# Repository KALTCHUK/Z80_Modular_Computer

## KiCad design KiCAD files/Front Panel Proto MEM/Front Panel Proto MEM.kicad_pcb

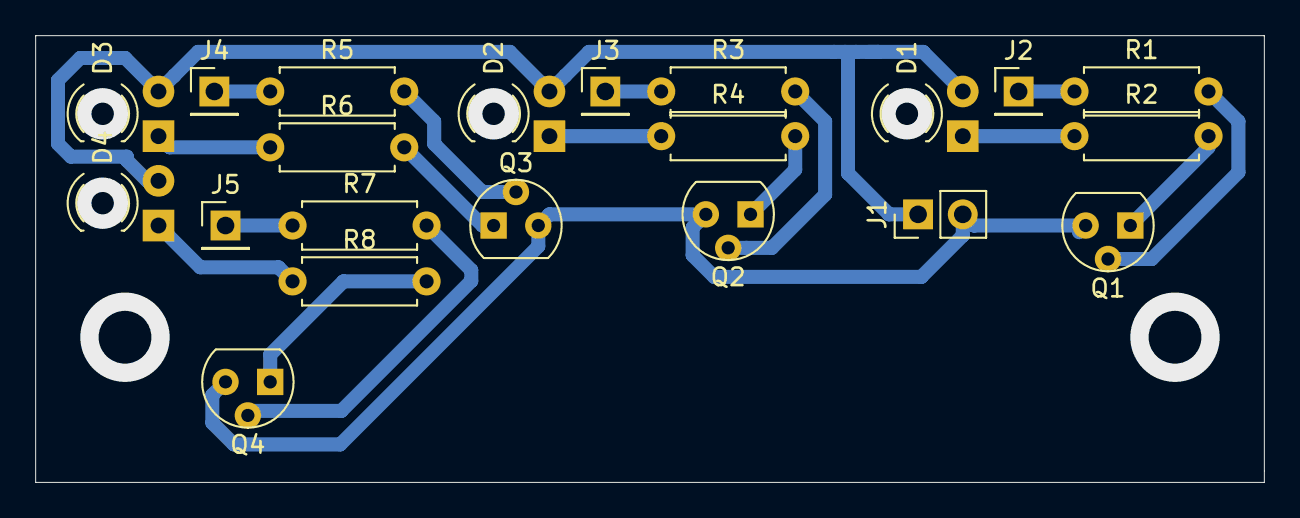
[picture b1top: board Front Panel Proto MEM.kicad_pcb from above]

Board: 2 copper layers, 69.9 x 25.4 mm, 21 parts (0 on the bottom side), 18 nets.

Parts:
D1, D2, D3, D4: LED; LED_D3.0mm
J1: Conn; PinHeader_1x02_P2.54mm_Vertical
J2, J3, J4, J5: Conn; PinHeader_1x01_P2.54mm_Vertical
Q1, Q2, Q3, Q4: BC547; TO-92_Inline
R1, R3, R5, R7: 10k; R_Axial_DIN0207_L6.3mm_D2.5mm_P7.62mm_Horizontal
R2, R4, R6, R8: 470; R_Axial_DIN0207_L6.3mm_D2.5mm_P7.62mm_Horizontal

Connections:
+5V: D1.2, D2.2, D3.2, D4.2, J1.1
GND: J1.2, Q1.3, Q2.3, Q3.3, Q4.3
unnamed: D1.1, R2.1
unnamed: D2.1, R4.1
unnamed: D3.1, R6.1
unnamed: D4.1, R8.1
unnamed: J2.1, R1.1
unnamed: J3.1, R3.1
unnamed: J4.1, R5.1
unnamed: J5.1, R7.1
unnamed: Q1.1, R2.2
unnamed: Q1.2, R1.2
unnamed: Q2.1, R4.2
unnamed: Q2.2, R3.2
unnamed: Q3.1, R6.2
unnamed: Q3.2, R5.2
unnamed: Q4.1, R8.2
unnamed: Q4.2, R7.2

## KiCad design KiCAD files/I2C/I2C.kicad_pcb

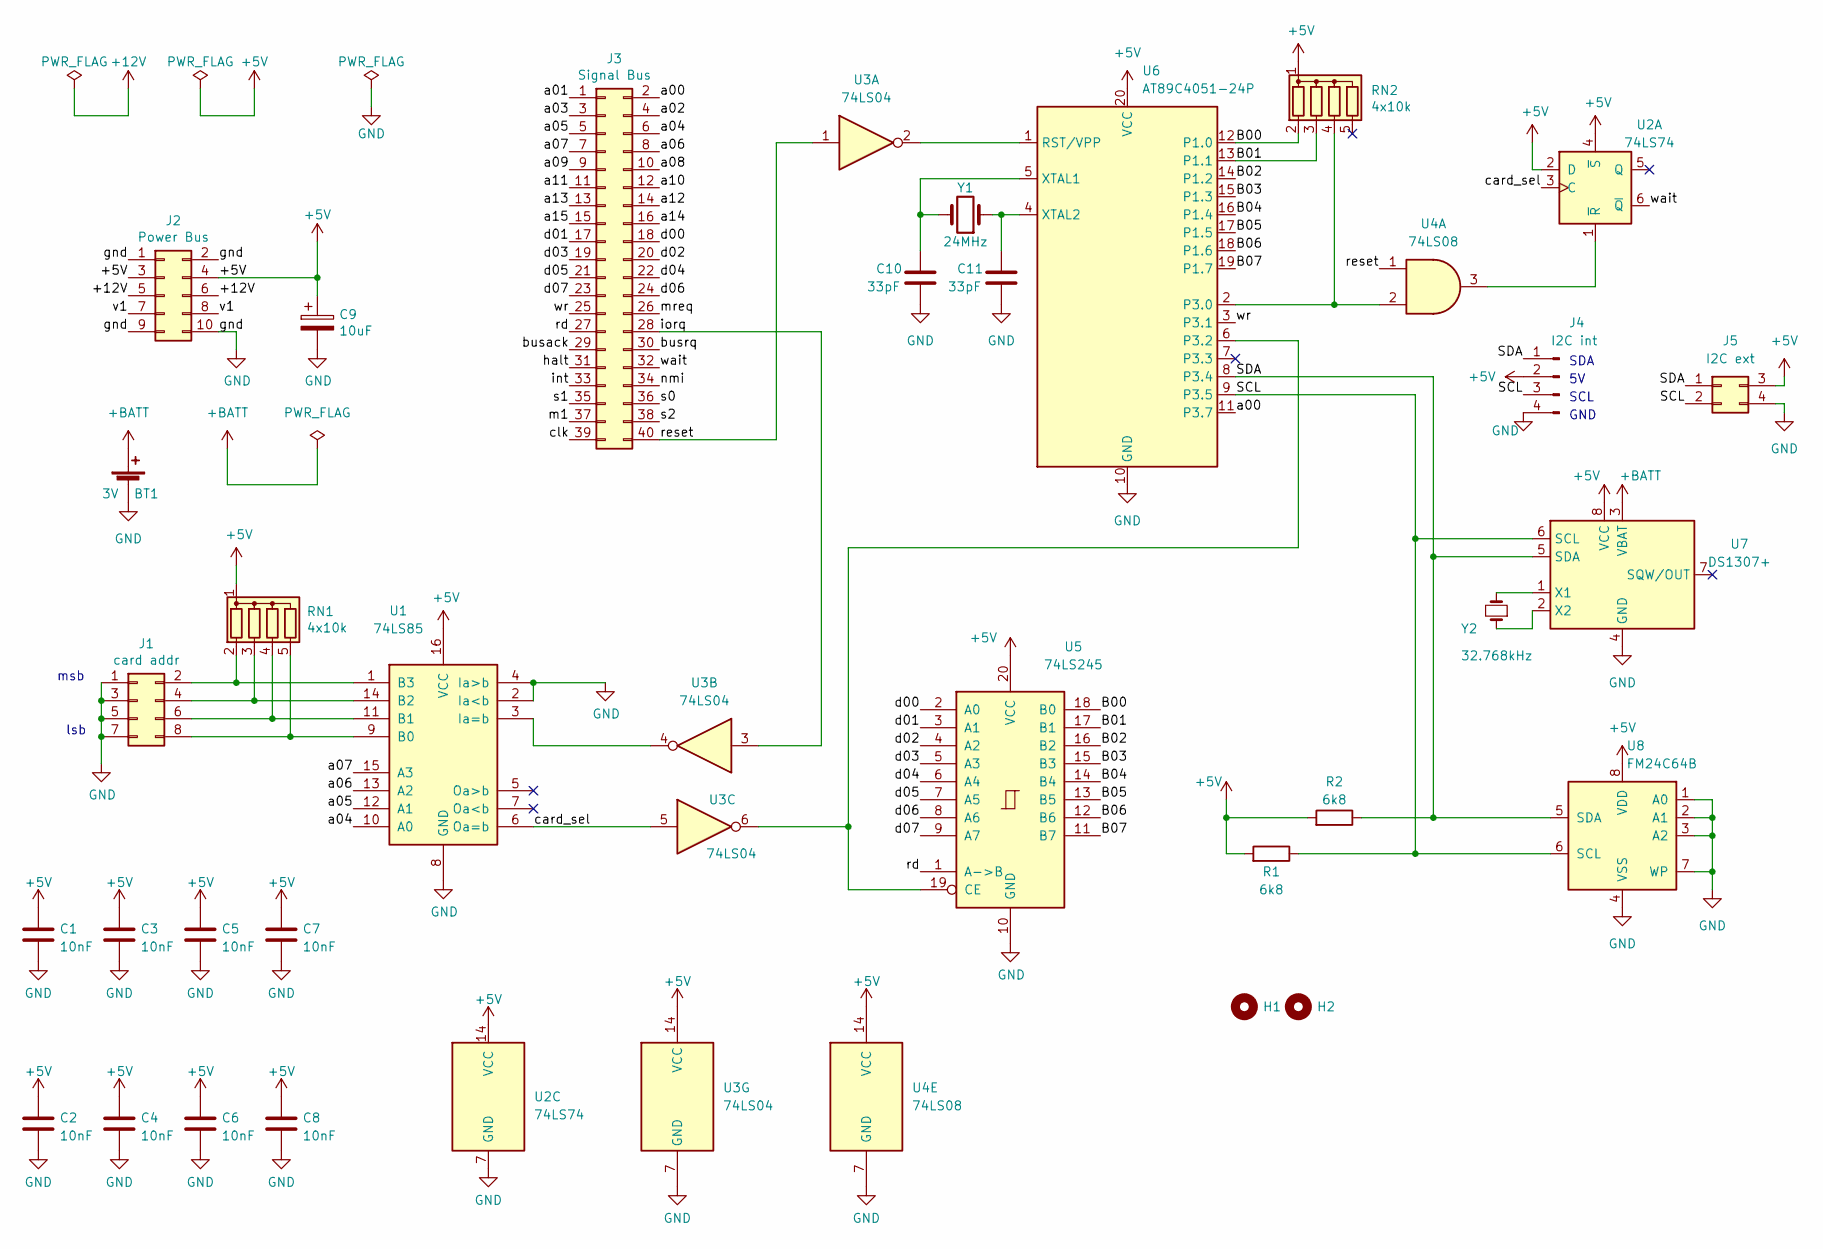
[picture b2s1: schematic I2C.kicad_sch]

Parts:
BT1: 3V; Battery-Holder_CR2032
C1, C2, C3, C4, C5, C6, C7, C8: 10nF; C_Disc_D3.8mm_W2.6mm_P2.50mm
C9: 10uF; CP_Radial_D5.0mm_P2.50mm
C10, C11: 33pF; C_Disc_D3.8mm_W2.6mm_P2.50mm
H1, H2: (no value)
J1: card addr; PinHeader_2x04_P2.54mm_Vertical
J2: Power Bus; PinHeader_2x05_P2.54mm_Vertical
J3: Signal Bus; PinHeader_2x20_P2.54mm_Vertical
J4: I2C int; PinHeader_1x04_P2.54mm_Vertical
J5: I2C ext; PinHeader_2x02_P2.54mm_Vertical
R1, R2: 6k8; R_Axial_DIN0207_L6.3mm_D2.5mm_P10.16mm_Horizontal
RN1, RN2: 4x10k; R_Array_SIP5
U1: 74LS85; DIP-16_W7.62mm_Socket_LongPads
U2: 74LS74; DIP-14_W7.62mm_Socket_LongPads
U3: 74LS04; DIP-14_W7.62mm_Socket_LongPads
U4: 74LS08; DIP-14_W7.62mm_Socket_LongPads
U5: 74LS245; DIP-20_W7.62mm_Socket_LongPads
U6: AT89C4051-24P; DIP-20_W7.62mm_Socket_LongPads
U7: DS1307+; DIP-8_W7.62mm_Socket_LongPads
U8: FM24C64B; DIP-8_W7.62mm_Socket_LongPads
Y1: 24MHz; Crystal_HC49-U_Vertical
Y2: 32.768kHz; Crystal_Round_D1.5mm_Vertical

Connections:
+5V: C1.1, C2.1, C3.1, C4.1, C5.1, C6.1, C7.1, C8.1, C9.1, J2.3, J2.4, J4.2, J5.3, R1.2, R2.2, RN1.1 (common), RN2.1 (common), U1.16 (VCC), U2.2 (D), U2.4 (~S), U2.14 (VCC), U3.14 (VCC), U4.14 (VCC), U5.20 (VCC), U6.20 (VCC), U7.8 (VCC), U8.8 (VDD)
+12V: J2.5, J2.6
+BATT: BT1.1 (+), U7.3 (VBAT)
/B00: RN2.2 (R1), U5.18 (B0), U6.12 (P1.0)
/B01: RN2.3 (R2), U5.17 (B1), U6.13 (P1.1)
/B02: U5.16 (B2), U6.14 (P1.2)
/B03: U5.15 (B3), U6.15 (P1.3)
/B04: U5.14 (B4), U6.16 (P1.4)
/B05: U5.13 (B5), U6.17 (P1.5)
/B06: U5.12 (B6), U6.18 (P1.6)
/B07: U5.11 (B7), U6.19 (P1.7)
/SCL: J4.3, J5.2, R1.1, U6.9 (P3.5), U7.6 (SCL), U8.6 (SCL)
/SDA: J4.1, J5.1, R2.1, U6.8 (P3.4), U7.5 (SDA), U8.5 (SDA)
/a00: J3.2, U6.11 (P3.7)
/a01: J3.1
/a02: J3.4
/a03: J3.3
/a04: J3.6, U1.10 (A0)
/a05: J3.5, U1.12 (A1)
/a06: J3.8, U1.13 (A2)
/a07: J3.7, U1.15 (A3)
/a08: J3.10
/a09: J3.9
/a10: J3.12
/a11: J3.11
/a12: J3.14
/a13: J3.13
/a14: J3.16
/a15: J3.15
/busack: J3.29
/busrq: J3.30
/card_sel: U1.6 (Oa=b), U2.3 (C), U3.5
/clk: J3.39
/d00: J3.18, U5.2 (A0)
/d01: J3.17, U5.3 (A1)
/d02: J3.20, U5.4 (A2)
/d03: J3.19, U5.5 (A3)
/d04: J3.22, U5.6 (A4)
/d05: J3.21, U5.7 (A5)
/d06: J3.24, U5.8 (A6)
/d07: J3.23, U5.9 (A7)
/halt: J3.31
/int: J3.33
/iorq: J3.28, U3.3
/m1: J3.37
/mreq: J3.26
/nmi: J3.34
/rd: J3.27, U5.1 (A->B)
/reset: J3.40, U3.1, U4.1
/s0: J3.36
/s1: J3.35
/s2: J3.38
/v1: J2.7, J2.8
/wait: J3.32, U2.6 (~Q)
/wr: J3.25, U6.3 (P3.1)
GND: BT1.2 (-), C1.2, C2.2, C3.2, C4.2, C5.2, C6.2, C7.2, C8.2, C9.2, C10.2, C11.2, J1.1, J1.3, J1.5, J1.7, J2.1, J2.2, J2.9, J2.10, J4.4, J5.4, U1.2 (Ia<b), U1.4 (Ia>b), U1.8 (GND), U2.7 (GND), U3.7 (GND), U4.7 (GND), U5.10 (GND), U6.10 (GND), U7.4 (GND), U8.1 (A0), U8.2 (A1), U8.3 (A2), U8.4 (VSS), U8.7 (WP)
unnamed: C10.1, U6.5 (XTAL1), Y1.2
unnamed: C11.1, U6.4 (XTAL2), Y1.1
unnamed: J1.2, RN1.2 (R1), U1.1 (B3)
unnamed: J1.4, RN1.3 (R2), U1.14 (B2)
unnamed: J1.6, RN1.4 (R3), U1.11 (B1)
unnamed: J1.8, RN1.5 (R4), U1.9 (B0)
unnamed: RN2.4 (R3), U4.2, U6.2 (P3.0)
unnamed: U1.3 (Ia=b), U3.4
unnamed: U2.1 (~R), U4.3
unnamed: U3.2, U6.1 (RST/VPP)
unnamed: U3.6, U5.19 (CE), U6.6 (P3.2)
unnamed: U7.1 (X1), Y2.2
unnamed: U7.2 (X2), Y2.1

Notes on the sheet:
SDA
msb
lsb
SCL
GND

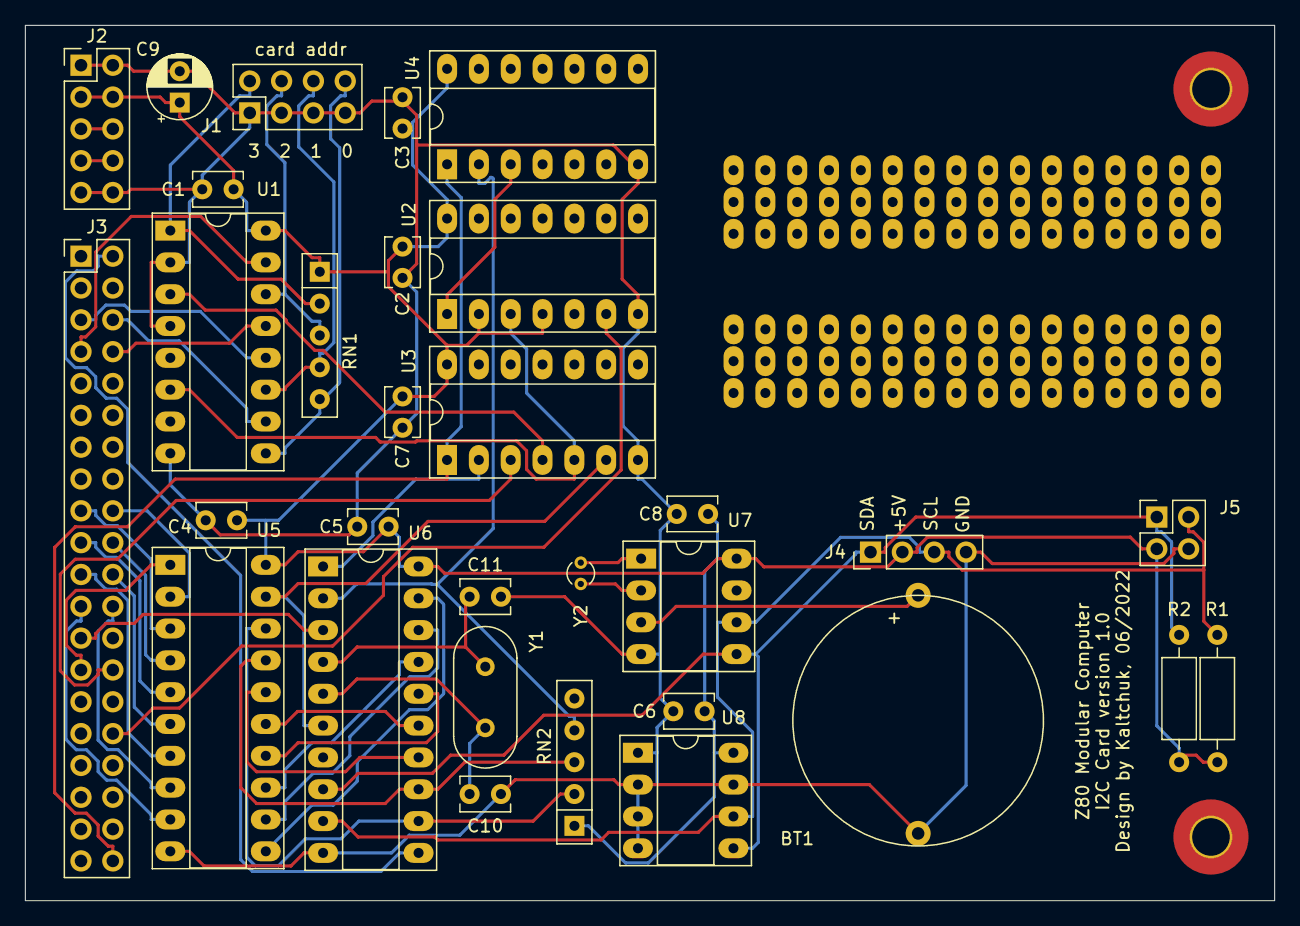
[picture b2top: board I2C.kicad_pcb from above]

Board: 2 copper layers, 99.7 x 69.8 mm, 33 parts (0 on the bottom side), 47 nets.

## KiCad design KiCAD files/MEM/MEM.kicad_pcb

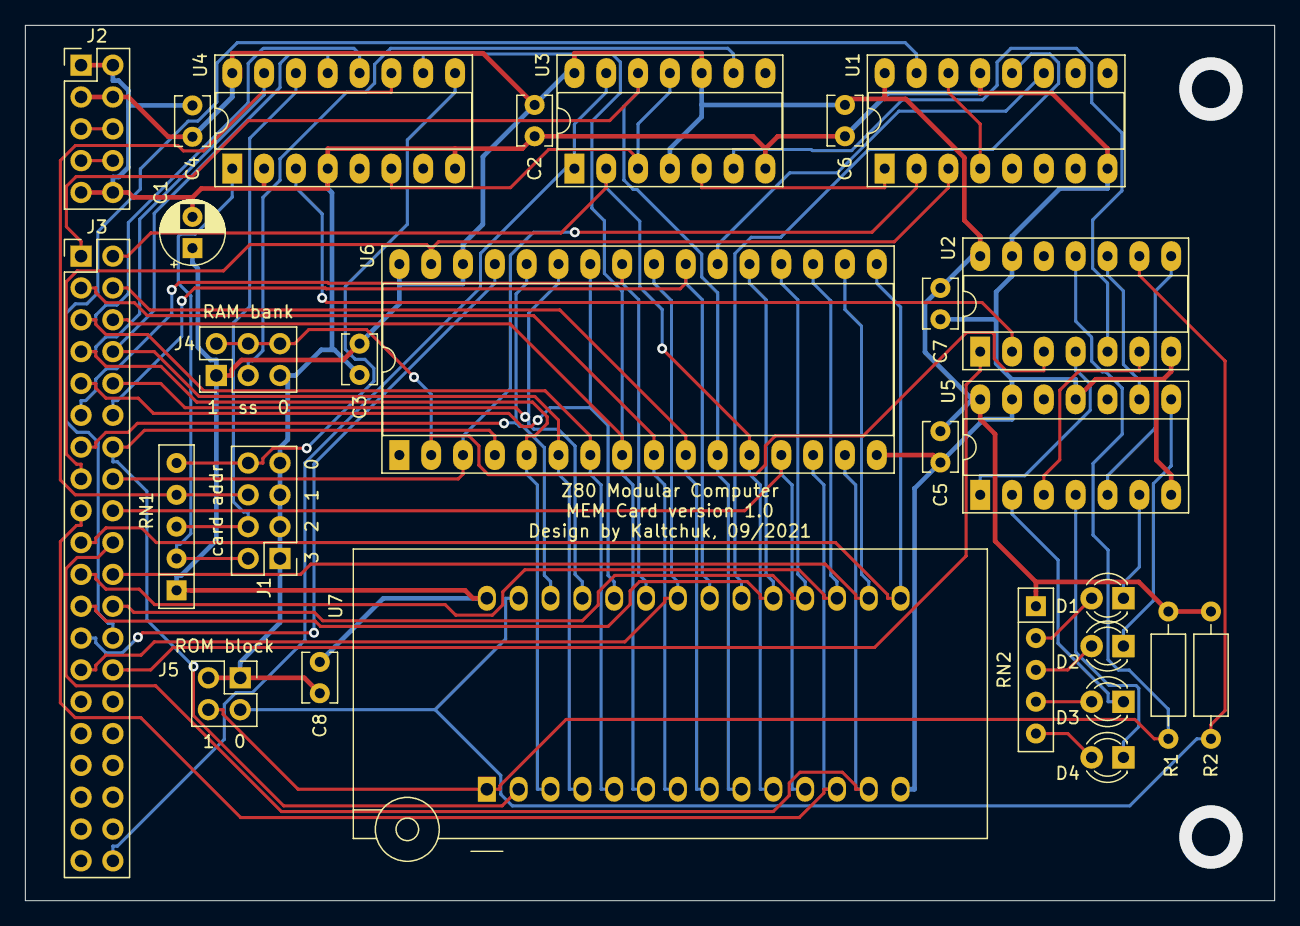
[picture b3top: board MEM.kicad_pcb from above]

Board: 2 copper layers, 99.7 x 69.8 mm, 28 parts (0 on the bottom side), 60 nets.

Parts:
C1: 10uF; CP_Radial_D5.0mm_P2.50mm
C2, C3, C4, C5, C6, C7, C8: 10nF; C_Disc_D3.8mm_W2.6mm_P2.50mm
D1, D2, D3, D4: LED; LED_D3.0mm
J1: card addr; PinHeader_2x04_P2.54mm_Vertical
J2: Power Bus; PinHeader_2x05_P2.54mm_Vertical
J3: Signal Bus; PinHeader_2x20_P2.54mm_Vertical
J4: RAM bank; PinHeader_2x03_P2.54mm_Vertical
J5: ROM block; PinHeader_2x02_P2.54mm_Vertical
R1, R2: 10k; R_Axial_DIN0207_L6.3mm_D2.5mm_P10.16mm_Horizontal
RN1: 4x10k; R_Array_SIP5
RN2: 4x220; R_Array_SIP5
U1: 74LS139; DIP-16_W7.62mm_Socket_LongPads
U2: 74LS04; DIP-14_W7.62mm_Socket_LongPads
U3: 74LS74; DIP-14_W7.62mm_Socket_LongPads
U4: 74LS85; DIP-16_W7.62mm_Socket_LongPads
U5: SN74LS07N; DIP-14_W7.62mm_Socket_LongPads
U6: 628128; DIP-32_W15.24mm_Socket_LongPads
U7: W27C512; DIP_Socket-28_W11.9_W12.7_W15.24_W17.78_W18.5_3M_228-1277-0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

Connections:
+5V: C1.1, C2.1, C3.1, C4.1, C5.1, C6.1, C7.1, C8.1, J2.3, J2.4, J4.1, R1.1, R2.1, RN1.1, RN2.1, U1.16, U2.14, U3.4, U3.10, U3.14, U4.16, U5.14, U6.30, U6.32, U7.28
/+12V: J2.5, J2.6
/a00: J3.2, U3.2, U6.12, U7.10
/a01: J3.1, U3.12, U6.11, U7.9
/a02: J3.4, U6.10, U7.8
/a03: J3.3, U6.9, U7.7
/a04: J3.6, U4.10, U6.8, U7.6
/a05: J3.5, U4.12, U6.7, U7.5
/a06: J3.8, U4.13, U6.6, U7.4
/a07: J3.7, U4.15, U6.5, U7.3
/a08: J3.10, U6.27, U7.25
/a09: J3.9, U6.26, U7.24
/a10: J3.12, U6.23, U7.21
/a11: J3.11, U6.25, U7.23
/a12: J3.14, U6.4, U7.2
/a13: J3.13, U6.28, U7.26
/a14: J3.16, U1.2, U6.3
/a15: J3.15, U1.3, U6.31
/d00: J3.18, U6.13, U7.11
/d01: J3.17, U6.14, U7.12
/d02: J3.20, U6.15, U7.13
/d03: J3.19, U6.17, U7.15
/d04: J3.22, U6.18, U7.16
/d05: J3.21, U6.19, U7.17
/d06: J3.24, U6.20, U7.18
/d07: J3.23, U6.21, U7.19
/iorq: J3.28, U2.1
/mreq: J3.26, U1.15
/ram_bank: J4.2, J4.4, J4.6, U2.3, U6.2
/rd: J3.27, U6.24, U7.22
/reset: J3.40, U3.1, U3.13
/v1: J2.7, J2.8
/wr: J3.25, U6.29
GND: C1.2, C2.2, C3.2, C4.2, C5.2, C6.2, C7.2, C8.2, J1.1, J1.3, J1.5, J1.7, J2.1, J2.2, J2.9, J2.10, J4.5, J5.1, J5.3, U1.8, U1.13, U2.7, U2.13, U3.7, U4.2, U4.4, U4.8, U5.7, U5.11, U5.13, U6.16, U7.14
unnamed: D1.1, U5.6
unnamed: D1.2, RN2.2
unnamed: D2.1, U5.8
unnamed: D2.2, RN2.3
unnamed: D3.1, U5.2
unnamed: D3.2, RN2.4
unnamed: D4.1, U5.4
unnamed: D4.2, RN2.5
unnamed: J1.2, RN1.2, U4.1
unnamed: J1.4, RN1.3, U4.14
unnamed: J1.6, RN1.4, U4.11
unnamed: J1.8, RN1.5, U4.9
unnamed: J4.3, U3.9
unnamed: J5.2, R2.2, U2.9, U7.27
unnamed: J5.4, R1.2, U2.11, U7.1
unnamed: U1.1, U3.5
unnamed: U1.11, U6.22
unnamed: U1.12, U7.20
unnamed: U1.4, U1.14
unnamed: U2.2, U4.3
unnamed: U2.4, U5.1
unnamed: U2.5, U3.6
unnamed: U2.6, U5.3
unnamed: U2.8, U5.5
unnamed: U2.10, U5.9
unnamed: U3.3, U3.11, U4.6

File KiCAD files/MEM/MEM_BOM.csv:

;;MEM BOM;;;;;
Id;Designator;Package;Quantity;Designation;Supplier;and;ref
1;J2;PinHeader_2x05_P2.54mm_Vertical;1;Power;Bus;;
2;C1;CP_Radial_D5.0mm_P2.50mm;1;10uF;;;
3;C2,C3,C4,C5,C6,C7,C8;C_Disc_D3.8mm_W2.6mm_P2.50mm;7;10nF;;;
4;D1,D2,D3,D4;LED_D3.0mm;4;LED;;;
5;J1;PinHeader_2x04_P2.54mm_Vertical;1;card;addr;;
6;J3;PinHeader_2x20_P2.54mm_Vertical;1;Signal;Bus;;
7;J5;PinHeader_2x02_P2.54mm_Vertical;1;ROM;block;;
8;R1,R2;R_Axial_DIN0207_L6.3mm_D2.5mm_P10.16mm_Horizontal;2;10k;;;
9;RN1;R_Array_SIP5;1;4x10k;;;
10;RN2;R_Array_SIP5;1;4x220;;;
11;U1;DIP-16_W7.62mm_Socket_LongPads;1;74LS139;;;
12;U2;DIP-14_W7.62mm_Socket_LongPads;1;74LS04;;;
13;U3;DIP-14_W7.62mm_Socket_LongPads;1;74LS74;;;
14;U4;DIP-16_W7.62mm_Socket_LongPads;1;74LS85;;;
15;U5;DIP-14_W7.62mm_Socket_LongPads;1;SN74LS07N;;;
16;U6;DIP-32_W15.24mm_Socket_LongPads;1;628128;;;
17;U7;DIP_Socket-28_W11.9_W12.7_W15.24_W17.78_W18.5_3M_228-1277-00-0602J;1;W27C512;;;
18;J4;PinHeader_2x03_P2.54mm_Vertical;1;RAM;bank;;
